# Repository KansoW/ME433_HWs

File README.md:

# ME433_2018

Go to the wiki to see the syllabus and schedule.

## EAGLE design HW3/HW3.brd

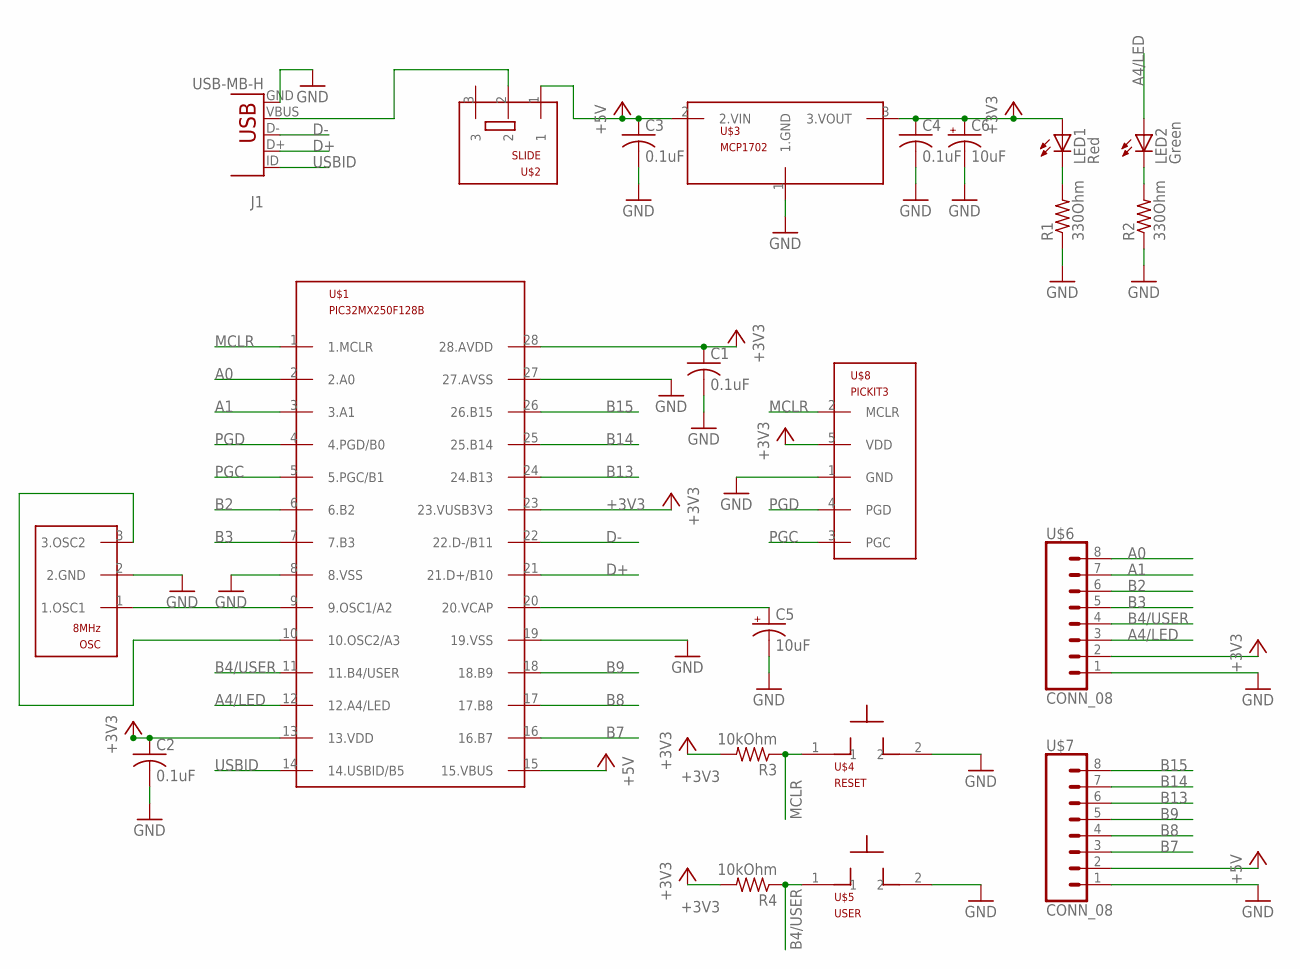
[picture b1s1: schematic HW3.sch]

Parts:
C1, C2, C3, C4: 0.1uF; C025-025X050
C5, C6: 10uF; B45181B
J1: USB-MB-H
LED1: Red; LED3MM
LED2: Green; LED3MM
OSC: 8MHz; OSC
R1, R2: 330Ohm; 0207/10
R3, R4: 10kOhm; 0207/10
U$1: PIC32MX250F128B; DIL28-3
U$2: SLIDE
U$3: MCP1702; TO92
U$4: RESET; PB
U$5: USER; PB
U$6, U$7: CONN_08; 1X08
U$8: PICKIT3; 1X05

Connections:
+3V3: C1.1, C2.1, C4.1, C6.+, LED1.A, R3.2, R4.2, U$1.13 (13.VDD), U$1.23 (23.VUSB3V3), U$1.28 (28.AVDD), U$3.3 (3.VOUT), U$6.2, U$8.5 (VDD)
+5V: C3.1, U$1.15 (15.VBUS), U$2.1, U$3.2 (2.VIN), U$7.2
A0: U$1.2 (2.A0), U$6.8
A1: U$1.3 (3.A1), U$6.7
A4/LED: LED2.A, U$1.12 (12.A4/LED), U$6.3
B2: U$1.6 (6.B2), U$6.6
B3: U$1.7 (7.B3), U$6.5
B4/USER: R4.1, U$1.11 (11.B4/USER), U$5.1, U$6.4
B7: U$1.16 (16.B7), U$7.3
B8: U$1.17 (17.B8), U$7.4
B9: U$1.18 (18.B9), U$7.5
B13: U$1.24 (24.B13), U$7.6
B14: U$1.25 (25.B14), U$7.7
B15: U$1.26 (26.B15), U$7.8
D+: J1.D+, U$1.21 (21.D+/B10)
D-: J1.D-, U$1.22 (22.D-/B11)
GND: C1.2, C2.2, C3.2, C4.2, C5.-, C6.-, J1.GND, OSC.2 (2.GND), R1.1, R2.1, U$1.8 (8.VSS), U$1.19 (19.VSS), U$1.27 (27.AVSS), U$3.1 (1.GND), U$4.2, U$5.2, U$6.1, U$7.1, U$8.1 (GND)
MCLR: R3.1, U$1.1 (1.MCLR), U$4.1, U$8.2 (MCLR)
unnamed: J1.VBUS, U$2.2
unnamed: LED1.K (C), R1.2
unnamed: LED2.K (C), R2.2
unnamed: OSC.1 (1.OSC1), U$1.9 (9.OSC1/A2)
unnamed: OSC.3 (3.OSC2), U$1.10 (10.OSC2/A3)
unnamed: C5.+, U$1.20 (20.VCAP)
PGC: U$1.5 (5.PGC/B1), U$8.3 (PGC)
PGD: U$1.4 (4.PGD/B0), U$8.4 (PGD)
USBID: J1.ID, U$1.14 (14.USBID/B5)

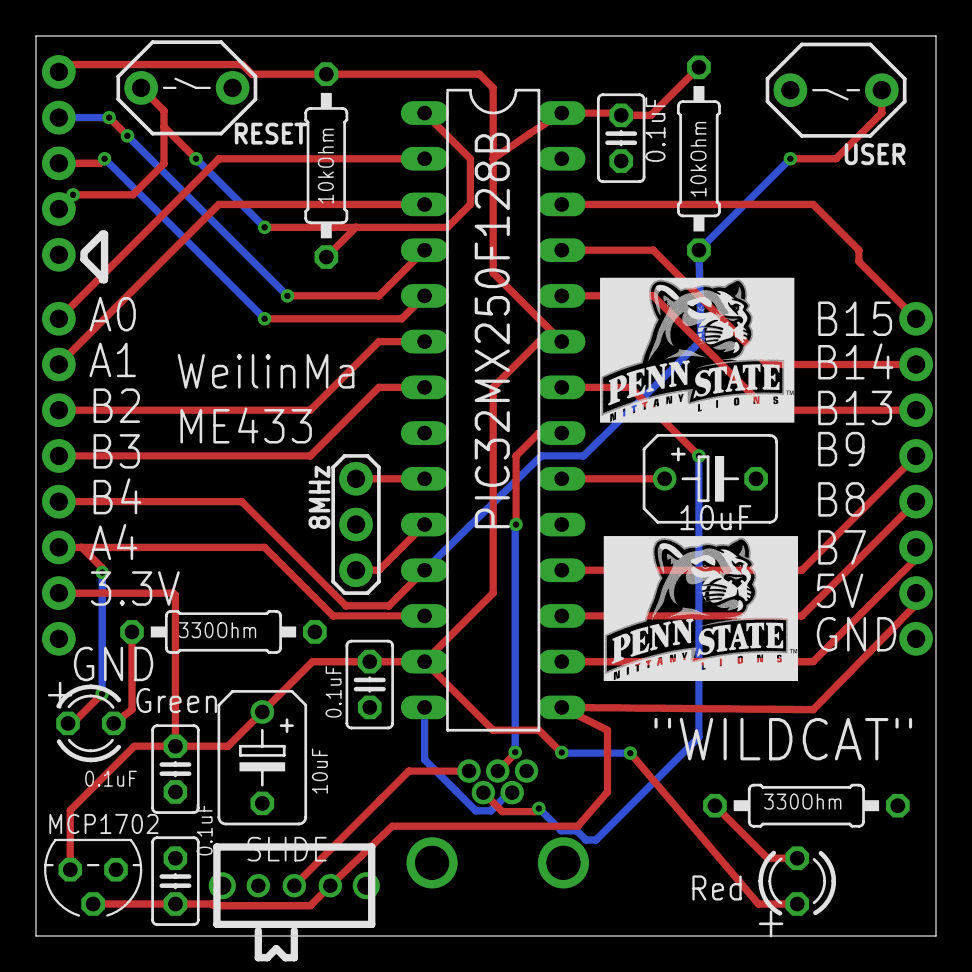
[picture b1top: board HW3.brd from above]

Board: 2 copper layers, 50.0 x 50.0 mm, 22 parts (1 on the bottom side), 27 nets.

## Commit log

2018-04-04 first
2018-04-12 added HW1
2018-04-17 added HW2
2018-04-17 finished HW3
2018-04-17 added bmp
2018-04-17 added board PDF
2018-04-17 remade logo
2018-05-01 added HW1 video
2018-05-15 start HW4
2018-05-20 added libraries
2018-05-21 changed libararies
2018-05-27 created HW5
2018-05-27 rebuilt HW5 project
2018-05-27 made changes to HW5
2018-05-28 made changes to HW6
2018-05-30 added HW5 schematics
2018-05-30 built HW7
2018-06-03 made changes to HW7
2018-06-03 started HW8
2018-06-03 tested harmony with HW1 code
2018-06-03 debugged something in HW8
2018-06-03 verified the IMU works in Harmony
2018-06-04 added HW9
2018-06-04 added IMU
2018-06-06 changes to IMU.h
2018-06-07 rebuilt HW9
2018-06-07 restarted HW9
2018-06-09 debugged HW9
2018-06-10 started HW10
2018-06-11 made changes to config
2018-06-11 debugging HW9
2018-06-11 made changes
2018-06-11 cleared out
2018-06-11 added plotting
2018-06-12 added HW11
2018-06-12 changed app.c to test mouse
2018-06-14 started HW12
2018-06-14 got the first version working
2018-06-14 made changes to main
2018-06-14 debugged app crush issue
2018-06-14 started HW13
2018-06-14 tested the first version
2018-06-14 finished HW13 and started HW15
2018-06-14 started HW14
2018-06-14 finished HW14
2018-06-14 started HW15
2018-06-14 modified HW16
2018-06-14 finished HW16
2018-06-14 made HW18
2018-06-14 added HW17 and camera app
2018-06-14 modified HW17
2018-06-15 added CAD files to HW18
2018-06-16 added detials for CAD design
2018-06-17 added final CAD
